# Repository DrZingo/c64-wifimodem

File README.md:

# c64-wifimodem

## src
Source code for my c64-wifimodem

Feel free to make changes and correction.

## Important
- Please change example.com to your own domain for OTA updates. 
- You will also have to create a backend for OTA to work.

## Stuff that needs work
- Changing pin polarity does not work as expected.
  - V-1541 and commodoreserver.com should work if implemented correct. I had it working, but then normal cbm polarity didn't work as it should.
- Higher baud rates
  - 19200 and 38400 will work but is only used with flipped polarity as I know of.
- Incoming calls
  - I am not enough familiar with bbs servers answering mechanism, and couldn't get it to work with my badly set up bbs server.
  - Direct call connection to the modem does work, sort of.
- S-registers
  - May be useful, I don't know.

## c64-wifimodem
PCB files in kicad format. Nothing much to say about it.

## BOM

```
 C1      Tantalum 22uF Case B, 3528
 J4      User Port edge connector
 Q1-Q5   BSS138 SOT-23
 R1-R12  10k 0805
 U1      LM1117-3.3 SOT-223
 U2      ESP8266 12E or 12F
 U3      OLED 0.96" GND,VCC,SCL,SDA
```

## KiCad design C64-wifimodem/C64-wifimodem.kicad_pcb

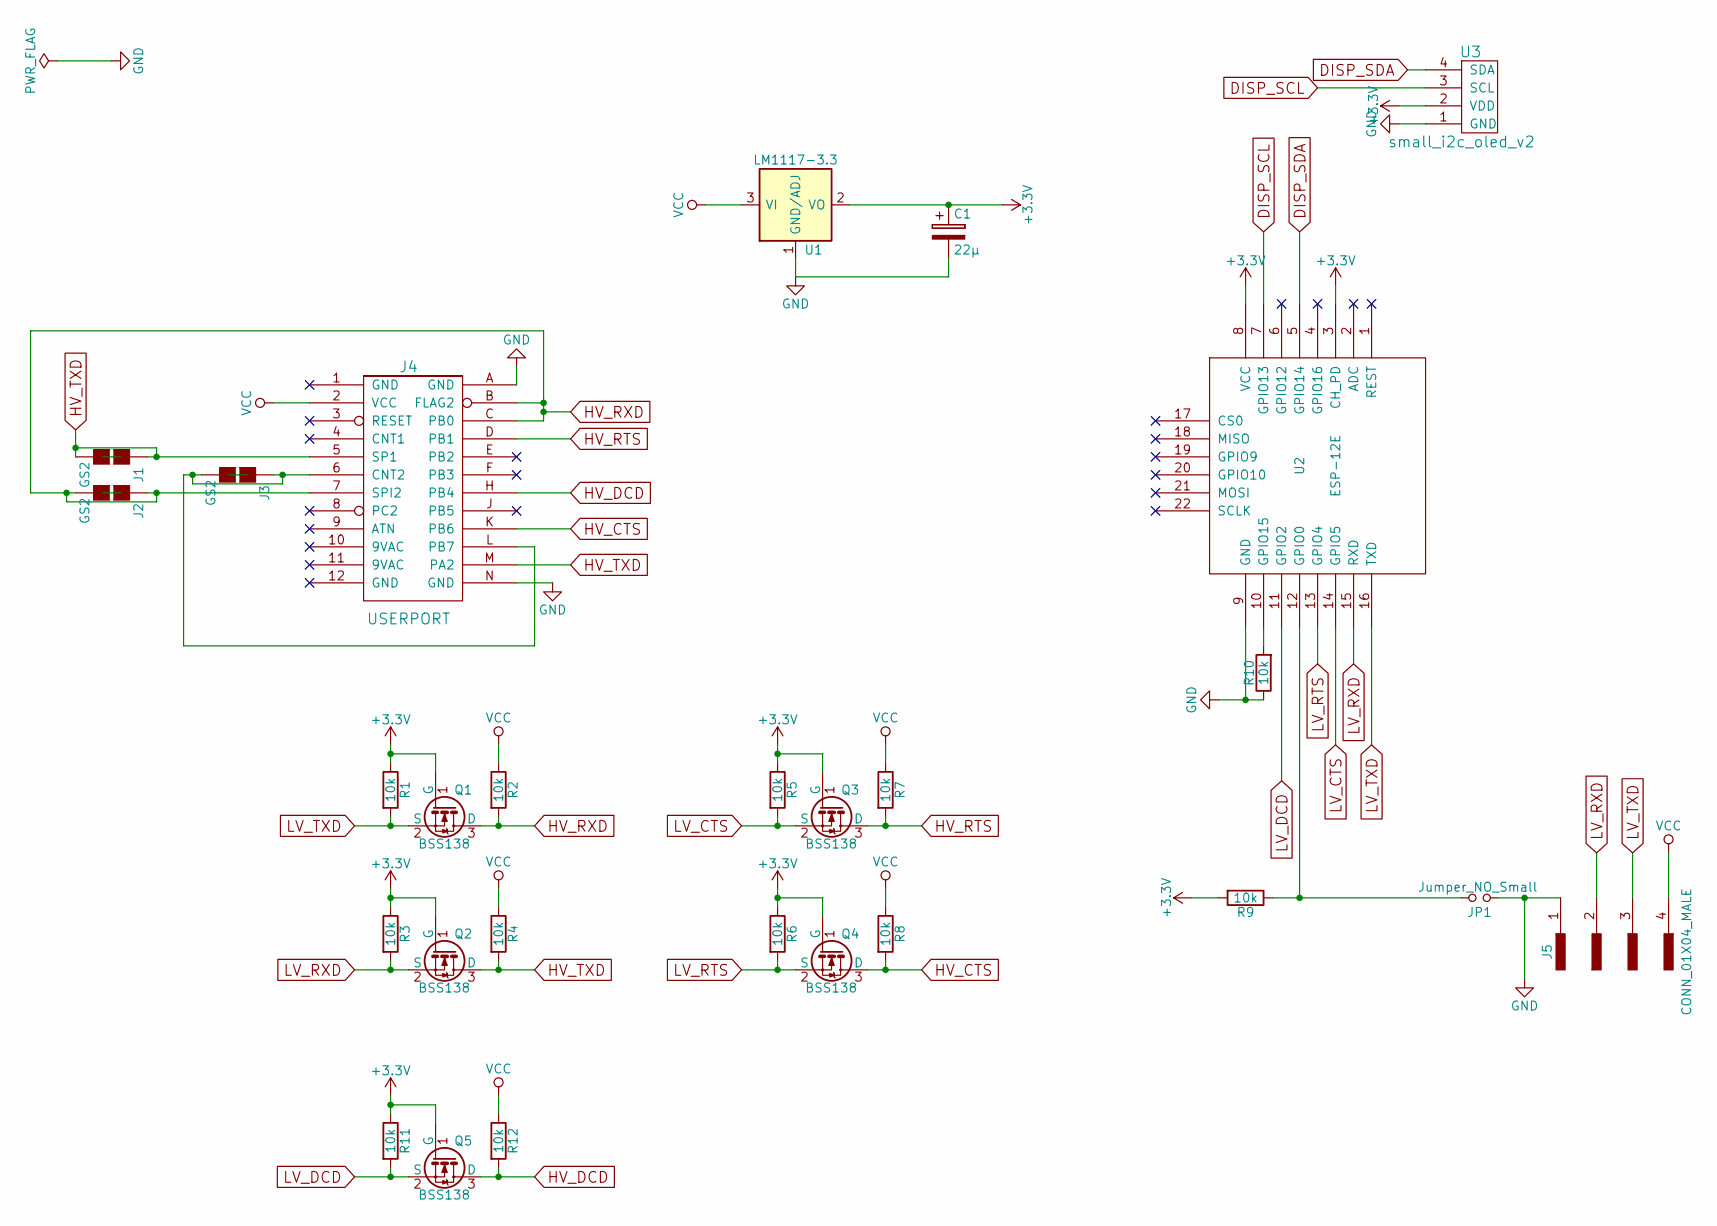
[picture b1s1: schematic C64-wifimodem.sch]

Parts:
C1: 22µ; CP_Tantalum_Case-B_EIA-3528-21_Hand
J1, J2, J3: GS2
J4: USERPORT
J5: CONN_01X04_MALE; Pin_Header_Straight_1x04_Pitch2.54mm
JP1: Jumper_NO_Small; Pin_Header_Straight_1x02_Pitch2.54mm
Q1, Q2, Q3, Q4, Q5: BSS138; SOT-23_Handsoldering
R1, R2, R3, R4, R5, R6, R7, R8, R9, R10, R11, R12: 10k; R_0805_HandSoldering
U1: LM1117-3.3; SOT-223
U2: ESP-12E; ESP-12E_SMD_wo_line
U3: small_i2c_oled_v2; Small_I2C_OLED_v2

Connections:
+3V3: C1.1, Q1.1 (G), Q2.1 (G), Q3.1 (G), Q4.1 (G), Q5.1 (G), R1.1, R3.1, R5.1, R6.1, R9.2, R11.1, U1.2 (VO), U1.4 (VO), U2.3 (CH_PD), U2.8 (VCC), U3.2 (VDD)
DISP_SCL: U2.7 (GPIO13), U3.3 (SCL)
DISP_SDA: U2.5 (GPIO14), U3.4 (SDA)
GND: C1.2, J4.A (GND), J4.N (GND), J5.1, JP1.1, R10.1, U1.1 (GND/ADJ), U2.9 (GND), U3.1 (GND)
HV_CTS: J4.K (PB6), Q4.3 (D), R8.2
HV_DCD: J4.H (PB4), Q5.3 (D), R12.2
HV_RTS: J4.D (PB1), Q3.3 (D), R7.2
HV_RXD: J2.1 (G1), J2.2 (G2), J4.7 (SPI2), J4.B (FLAG2), J4.C (PB0), Q1.3 (D), R2.2
HV_TXD: J1.1 (G1), J1.2 (G2), J4.5 (SP1), J4.M (PA2), Q2.3 (D), R4.2
LV_CTS: Q3.2 (S), R5.2, U2.14 (GPIO5)
LV_DCD: Q5.2 (S), R11.2, U2.11 (GPIO2)
LV_RTS: Q4.2 (S), R6.2, U2.13 (GPIO4)
LV_RXD: J5.2, Q2.2 (S), R3.2, U2.15 (RXD)
LV_TXD: J5.3, Q1.2 (S), R1.2, U2.16 (TXD)
unnamed: J3.1 (G1), J3.2 (G2), J4.6 (CNT2), J4.L (PB7)
unnamed: JP1.2, R9.1, U2.12 (GPIO0)
unnamed: R10.2, U2.10 (GPIO15)
VCC: J4.2 (VCC), J5.4, R2.1, R4.1, R7.1, R8.1, R12.1, U1.3 (VI)

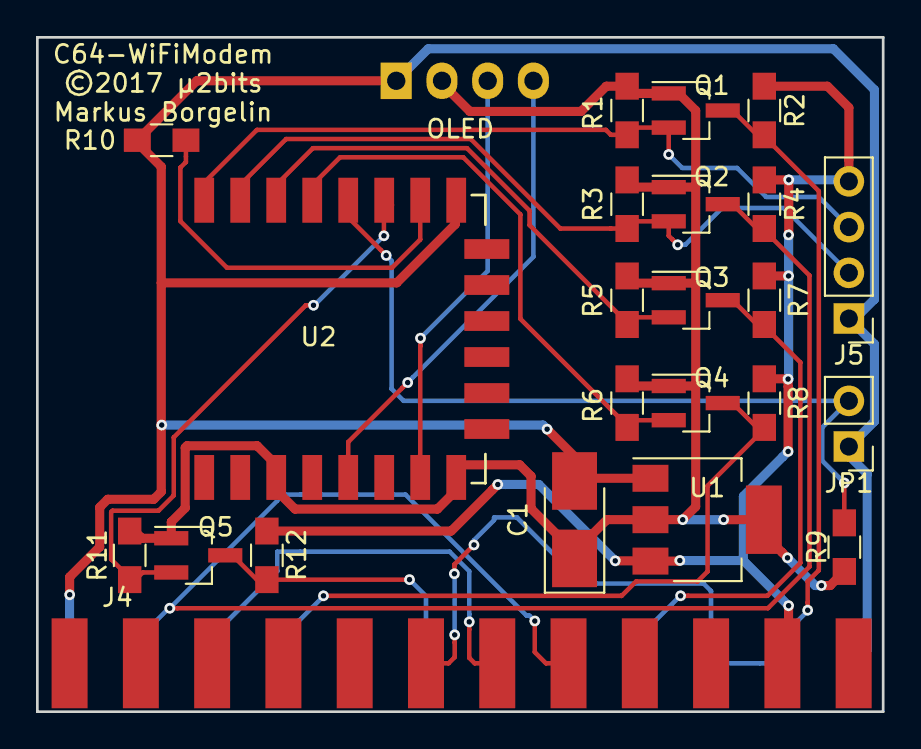
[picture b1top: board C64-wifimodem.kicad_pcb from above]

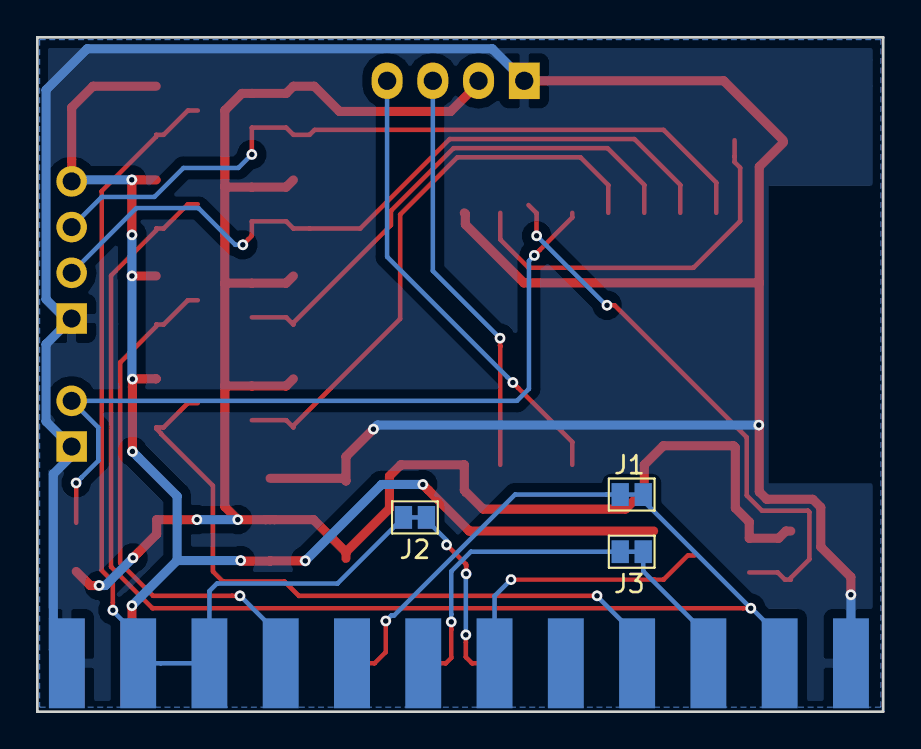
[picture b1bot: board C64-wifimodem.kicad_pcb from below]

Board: 2 copper layers, 47.0 x 37.5 mm, 27 parts (3 on the bottom side), 18 nets.

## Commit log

2018-12-29 Add README notes
2018-12-29 Add initial source code
2018-12-29 Add "Stuff that needs work"
2018-12-29 Add kicad files
2018-12-29 Add manual
2018-12-30 Add BOM
2019-01-03 Fix BOM
2019-05-30 added esp32 port

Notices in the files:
C64-wifimodem/C64-wifimodem.kicad_pcb:
©2017 µ2bits
